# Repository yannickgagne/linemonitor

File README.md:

# linemonitor

Little project I made to monitor my phone line at home. The circuit detects when the phone goes off-hook and on-hook and output a logic level that can be monitored with a GPIO
 on an Arduino or Raspberry Pi easily.

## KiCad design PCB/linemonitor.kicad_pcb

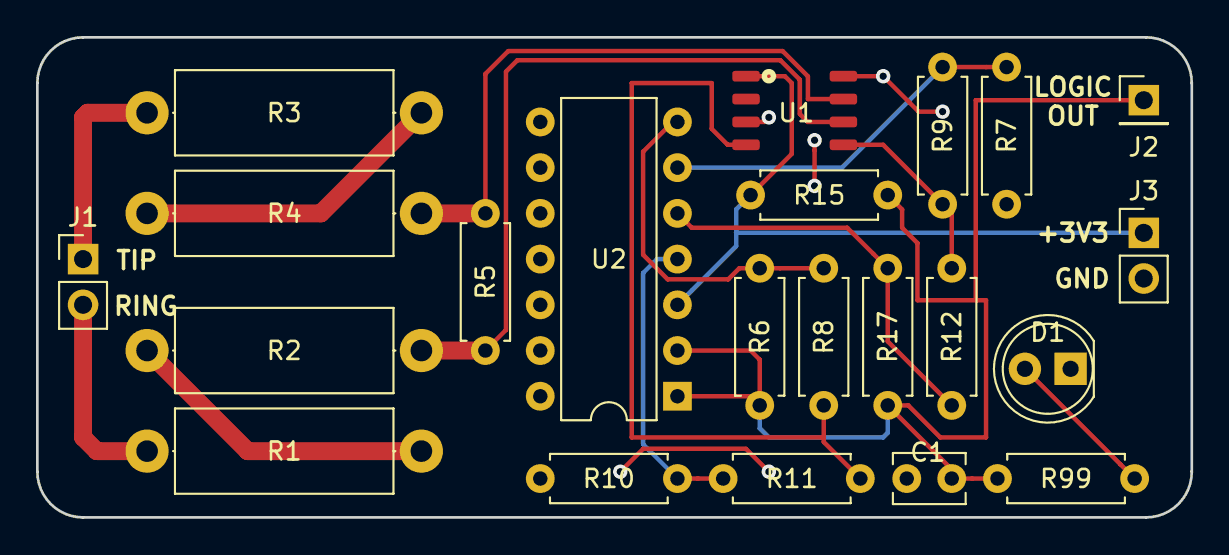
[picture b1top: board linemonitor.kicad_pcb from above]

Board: 2 copper layers, 64.1 x 26.7 mm, 22 parts (0 on the bottom side), 16 nets.

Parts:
C1: 1nF; C_Disc_D3.8mm_W2.6mm_P2.50mm
D1: LED; LED_D5.0mm_Clear
J1, J3: Conn_01x02; PinHeader_1x02_P2.54mm_Vertical
J2: Conn_01x01; PinHeader_1x01_P2.54mm_Vertical
R1, R2, R3, R4: 8.06M; R_Axial_DIN0414_L11.9mm_D4.5mm_P15.24mm_Horizontal
R5: 604K; R_Axial_DIN0207_L6.3mm_D2.5mm_P7.62mm_Horizontal
R6, R17: 4.7M; R_Axial_DIN0207_L6.3mm_D2.5mm_P7.62mm_Horizontal
R7, R10: 21K; R_Axial_DIN0207_L6.3mm_D2.5mm_P7.62mm_Horizontal
R8, R12: 20K; R_Axial_DIN0207_L6.3mm_D2.5mm_P7.62mm_Horizontal
R9, R11: 499K; R_Axial_DIN0207_L6.3mm_D2.5mm_P7.62mm_Horizontal
R15: 10K; R_Axial_DIN0207_L6.3mm_D2.5mm_P7.62mm_Horizontal
R99: 68; R_Axial_DIN0207_L6.3mm_D2.5mm_P7.62mm_Horizontal
U1: CPC5710N
U2: LM339; DIP-14_W7.62mm

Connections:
+3V3: J3.1, R15.2, U1.1, U2.3
GNDREF: C1.2, D1.1, J3.2, R7.2, R10.2, U1.3, U1.8, U2.12
unnamed: C1.1, J2.1, R6.1, R15.1, R17.1, R99.1, U2.1, U2.2
unnamed: D1.2, R99.2
unnamed: J1.1, R3.2
unnamed: J1.2, R1.2
unnamed: R1.1, R2.2
unnamed: R2.1, R5.1, U1.6
unnamed: R3.1, R4.2
unnamed: R4.1, R5.2, U1.7
unnamed: R6.2, R8.1, U2.7
unnamed: R7.1, R9.1, U2.6
unnamed: R10.1, R11.2, U2.4
unnamed: R8.2, R11.1, U1.4
unnamed: R12.1, R17.2, U2.5
unnamed: R9.2, R12.2, U1.5

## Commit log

2019-03-24 modif gitignore
2019-03-24 added datasheet
2019-03-24 test
2019-03-24 test 2
2019-03-24 description
2019-03-27 small mods + pdf
